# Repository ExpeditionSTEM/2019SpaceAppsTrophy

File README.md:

# 2019SpaceAppsTrophy

PLEASE STAY TUNED FOR UPDATES!  I WILL GET THIS REPO UPDATED BY 10/29.

A description of the 2019 Space Apps Trophy made for the Huntsville Main Stage

LIST OF COMPONENTS:

CUSTOM:

Custom Printed Circuit Board (PCB) - Designed by Andrew Denio.  Produced by JLCPCB.com  See "EAGLE" folder for files.

FROM ADAFRUIT:

Adafruit Feather 32u4 Bluefruit LE with Stacking Headers - Assembled (PID: 3242)
https://www.adafruit.com/product/3242

Adafruit 2.13" Monochrome eInk / ePaper Display FeatherWing - 250x122 Monochrome (PID: 4195)
https://www.adafruit.com/product/4195

Adafruit ADXL343 + ADT7410 Sensor FeatherWing (PID: 4147)
https://www.adafruit.com/product/4147

Adafruit 0.54" Quad Alphanumeric FeatherWing Display - Red (PID: 3130)
https://www.adafruit.com/product/3130

Lithium Ion Cylindrical Battery - 3.7v 2200mAh (PID: 1781)
https://www.adafruit.com/product/1781

FeatherWing Proto - Prototyping Add-on For All Feather Boards (PID: 2884)
https://www.adafruit.com/product/2884

Short Headers Kit for Feather - 12-pin + 16-pin Female Headers (PID: 2940)
https://www.adafruit.com/product/2940

Stacking Headers for Feather - 12-pin and 16-pin female headers (PID: 2830)
https://www.adafruit.com/product/2830

MISC:

Photoresistor (Light Sensor) 5 mm GM5539 5539
https://www.amazon.com/dp/B01N7V536K

Slide Switch 3 Pin 2 Position SPDT with PCB Panel for Arduino 0.5 Amp, 50V DC, 2 mm
https://www.amazon.com/gp/product/B079D58DB3/

FROM JLCPCB (mounted through SMT assembly):

WS2812B-V3 - 5050 LIGHT EMITTING DIODE (LED) RED/GREEN/BLUE SMD

TACTILE SWITCHES SPST 5.10MM X 5.10MM 0.40MM 50MA @ 12VDC SMD 

Multilayer Ceramic Capacitor - SMD/SMT 10UF 25V 0805 ROHS

CHIP RESISTOR - SURFACE MOUNT 10KOHMS ±1% 1/8W 0805 ROHS

CHIP RESISTOR - SURFACE MOUNT 470OHMS ±1% 1/8W 0805 ROHS

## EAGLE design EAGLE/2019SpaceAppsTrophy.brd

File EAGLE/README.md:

This folder contains the files needed to view the PCB in Autodesk Eagle

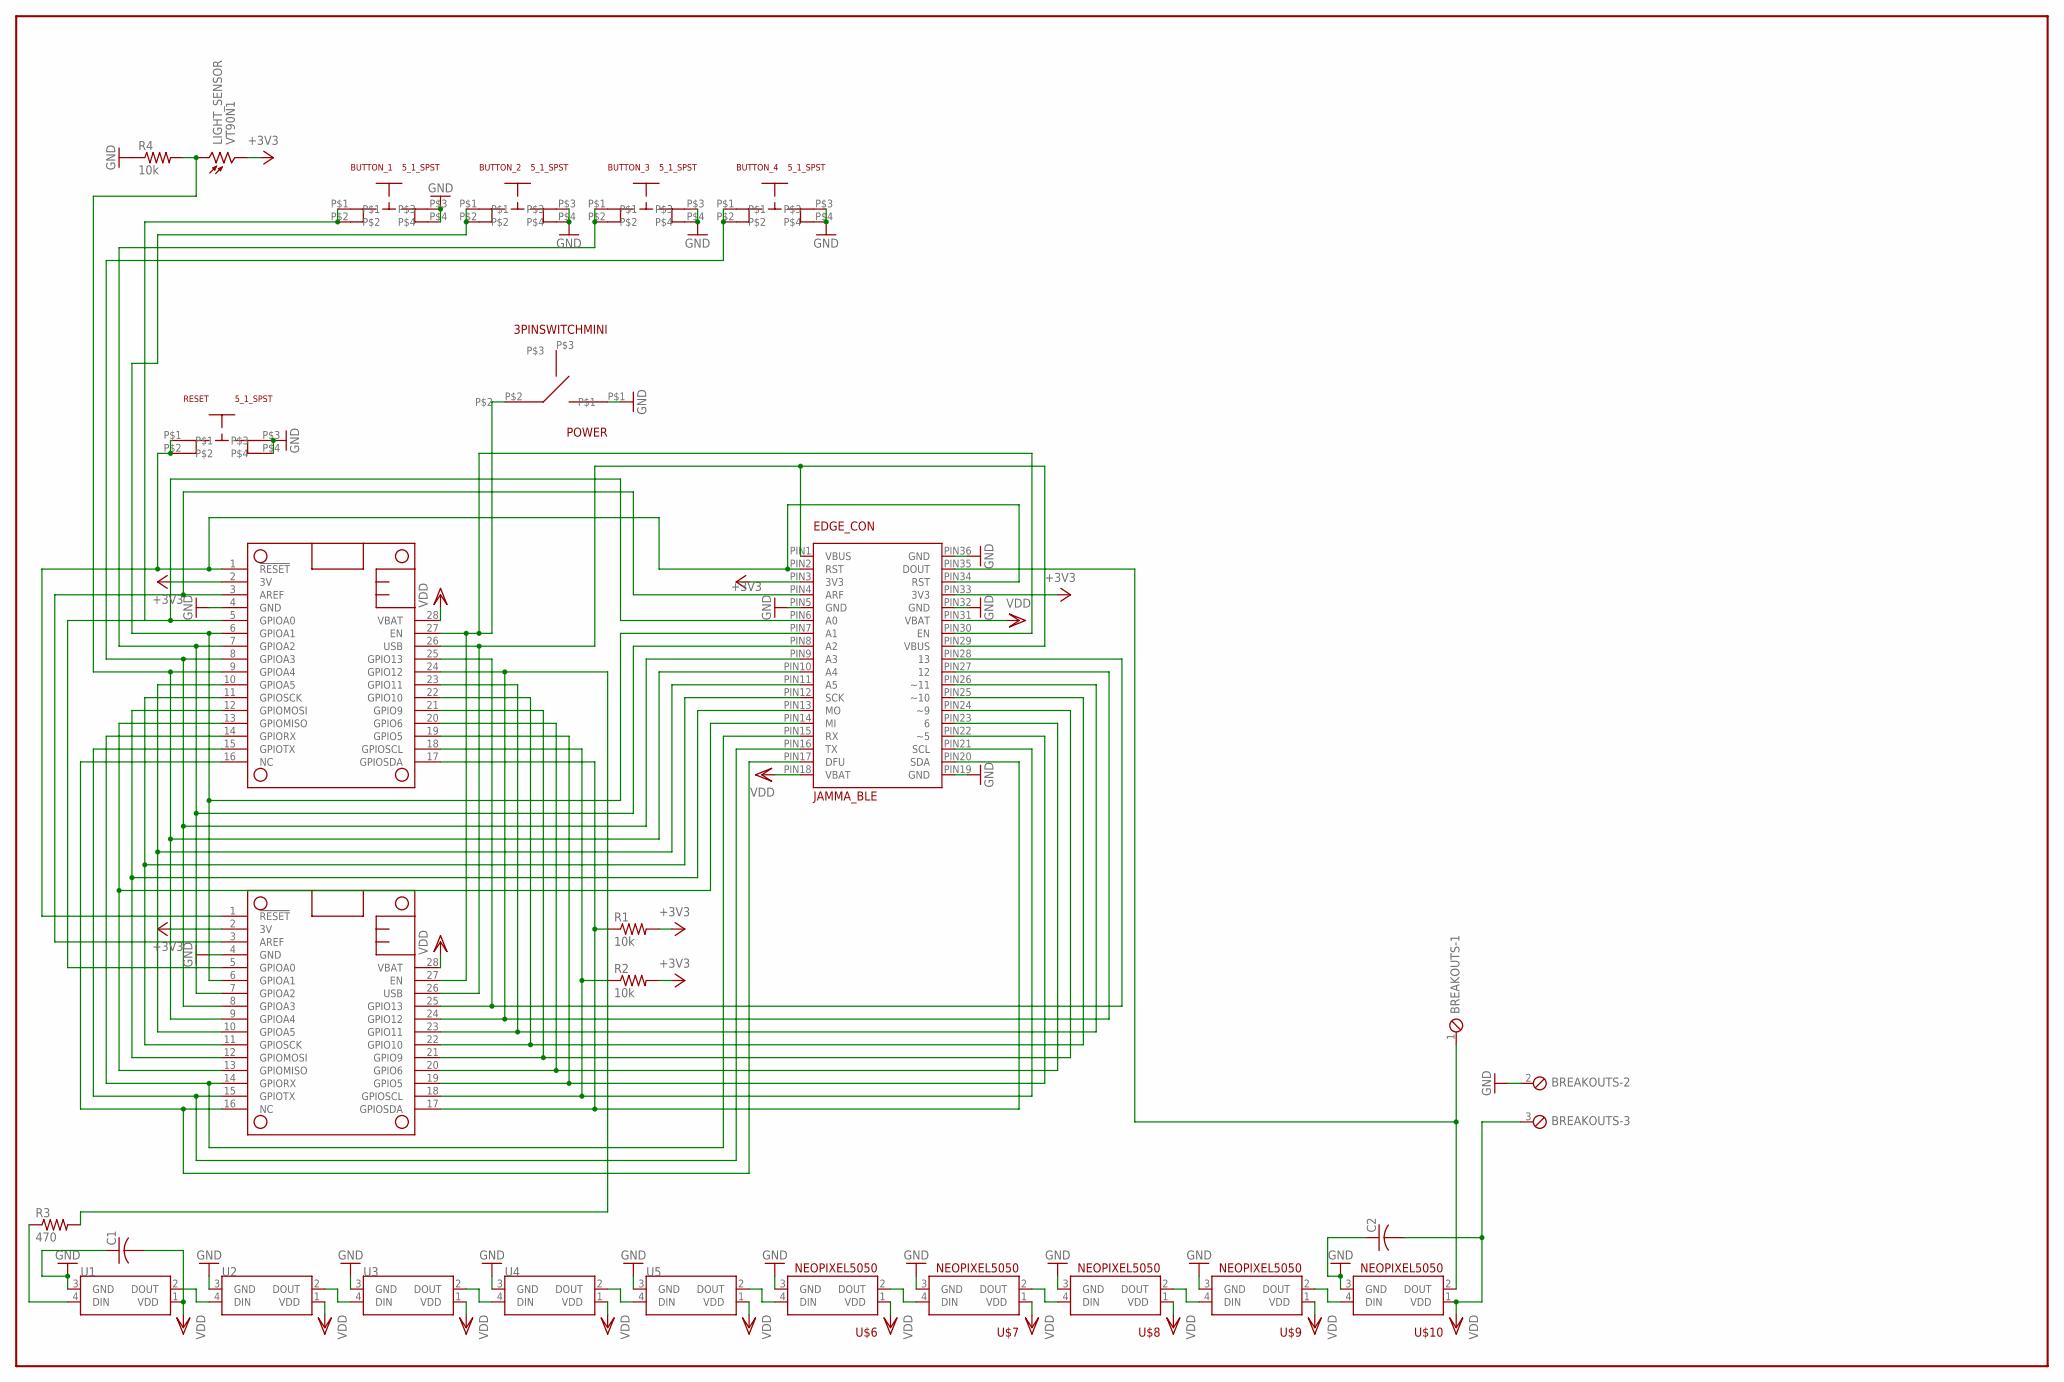
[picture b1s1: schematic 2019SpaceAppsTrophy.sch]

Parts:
BREAKOUTS: MPT3; 3POL254
BUTTON_1, BUTTON_2, BUTTON_3, BUTTON_4: 5_1_SPST
C1, C2: C-USC0805; C0805
EDGE_CON: JAMMA_BLE; JAMMA-28/56
LIGHT_SENSOR: VT90N1; VT900
MS2: FEATHERWING
POWER: 3PINSWITCHMINI; 3PINMINI
PROTOBOARD: FEATHERWING
R1, R2, R4: 10k; M0805
R3: 470; M0805
RESET: 5_1_SPST
U$1, U$2, U$3, U$4, U$5, U$6, U$7, U$8, U$9, U$10: NEOPIXEL5050

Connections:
+3V3: EDGE_CON.PIN3 (3V3), EDGE_CON.PIN33 (3V3), LIGHT_SENSOR.2, MS2.2 (3V), PROTOBOARD.2 (3V), R1.2, R2.2
GND: BREAKOUTS.2, BUTTON_1.P$3, BUTTON_1.P$4, BUTTON_2.P$3, BUTTON_2.P$4, BUTTON_3.P$3, BUTTON_3.P$4, BUTTON_4.P$3, BUTTON_4.P$4, C1.1, C2.1, EDGE_CON.PIN5 (GND), EDGE_CON.PIN19 (GND), EDGE_CON.PIN32 (GND), EDGE_CON.PIN36 (GND), MS2.4 (GND), POWER.P$1, PROTOBOARD.4 (GND), R4.1, RESET.P$3, RESET.P$4, U$1.3 (GND), U$2.3 (GND), U$3.3 (GND), U$4.3 (GND), U$5.3 (GND), U$6.3 (GND), U$7.3 (GND), U$8.3 (GND), U$9.3 (GND), U$10.3 (GND)
unnamed: EDGE_CON.PIN17 (DFU), MS2.16 (NC), PROTOBOARD.16 (NC)
unnamed: EDGE_CON.PIN16 (TX), MS2.15 (GPIOTX), PROTOBOARD.15 (GPIOTX)
unnamed: EDGE_CON.PIN15 (RX), MS2.14 (GPIORX), PROTOBOARD.14 (GPIORX)
unnamed: EDGE_CON.PIN14 (MI), MS2.13 (GPIOMISO), PROTOBOARD.13 (GPIOMISO)
unnamed: EDGE_CON.PIN13 (MO), MS2.12 (GPIOMOSI), PROTOBOARD.12 (GPIOMOSI)
unnamed: U$7.2 (DOUT), U$8.4 (DIN)
unnamed: EDGE_CON.PIN11 (A5), MS2.10 (GPIOA5), PROTOBOARD.10 (GPIOA5)
unnamed: EDGE_CON.PIN10 (A4), LIGHT_SENSOR.1, MS2.9 (GPIOA4), PROTOBOARD.9 (GPIOA4), R4.2
unnamed: BUTTON_4.P$1, BUTTON_4.P$2, EDGE_CON.PIN9 (A3), MS2.8 (GPIOA3), PROTOBOARD.8 (GPIOA3)
unnamed: BUTTON_3.P$1, BUTTON_3.P$2, EDGE_CON.PIN8 (A2), MS2.7 (GPIOA2), PROTOBOARD.7 (GPIOA2)
unnamed: BUTTON_2.P$1, BUTTON_2.P$2, EDGE_CON.PIN7 (A1), MS2.6 (GPIOA1), PROTOBOARD.6 (GPIOA1)
unnamed: BUTTON_1.P$1, BUTTON_1.P$2, EDGE_CON.PIN6 (A0), MS2.5 (GPIOA0), PROTOBOARD.5 (GPIOA0)
unnamed: EDGE_CON.PIN4 (ARF), MS2.3 (AREF), PROTOBOARD.3 (AREF)
unnamed: EDGE_CON.PIN2 (RST), EDGE_CON.PIN34 (RST), MS2.1 (!RESET), PROTOBOARD.1 (!RESET), RESET.P$1, RESET.P$2
unnamed: U$8.2 (DOUT), U$9.4 (DIN)
unnamed: EDGE_CON.PIN28 (13), MS2.25 (GPIO13), PROTOBOARD.25 (GPIO13)
unnamed: EDGE_CON.PIN27 (12), MS2.24 (GPIO12), PROTOBOARD.24 (GPIO12), R3.2
unnamed: EDGE_CON.PIN26 (~11), MS2.23 (GPIO11), PROTOBOARD.23 (GPIO11)
unnamed: EDGE_CON.PIN25 (~10), MS2.22 (GPIO10), PROTOBOARD.22 (GPIO10)
unnamed: EDGE_CON.PIN24 (~9), MS2.21 (GPIO9), PROTOBOARD.21 (GPIO9)
unnamed: EDGE_CON.PIN23 (6), MS2.20 (GPIO6), PROTOBOARD.20 (GPIO6)
unnamed: EDGE_CON.PIN22 (~5), MS2.19 (GPIO5), PROTOBOARD.19 (GPIO5)
unnamed: EDGE_CON.PIN21 (SCL), MS2.18 (GPIOSCL), PROTOBOARD.18 (GPIOSCL), R2.1
unnamed: EDGE_CON.PIN20 (SDA), MS2.17 (GPIOSDA), PROTOBOARD.17 (GPIOSDA), R1.1
unnamed: U$9.2 (DOUT), U$10.4 (DIN)
unnamed: U$1.2 (DOUT), U$2.4 (DIN)
unnamed: U$2.2 (DOUT), U$3.4 (DIN)
unnamed: U$3.2 (DOUT), U$4.4 (DIN)
unnamed: U$4.2 (DOUT), U$5.4 (DIN)
unnamed: U$6.2 (DOUT), U$7.4 (DIN)
unnamed: U$5.2 (DOUT), U$6.4 (DIN)
unnamed: BREAKOUTS.1, EDGE_CON.PIN35 (DOUT), U$10.2 (DOUT)
unnamed: EDGE_CON.PIN12 (SCK), MS2.11 (GPIOSCK), PROTOBOARD.11 (GPIOSCK)
unnamed: R3.1, U$1.4 (DIN)
unnamed: EDGE_CON.PIN30 (EN), MS2.27 (EN), POWER.P$2, PROTOBOARD.27 (EN)
USB: EDGE_CON.PIN1 (VBUS), EDGE_CON.PIN29 (VBUS), MS2.26 (USB), PROTOBOARD.26 (USB)
VDD: BREAKOUTS.3, C1.2, C2.2, EDGE_CON.PIN18 (VBAT), EDGE_CON.PIN31 (VBAT), MS2.28 (VBAT), PROTOBOARD.28 (VBAT), U$1.1 (VDD), U$2.1 (VDD), U$3.1 (VDD), U$4.1 (VDD), U$5.1 (VDD), U$6.1 (VDD), U$7.1 (VDD), U$8.1 (VDD), U$9.1 (VDD), U$10.1 (VDD)

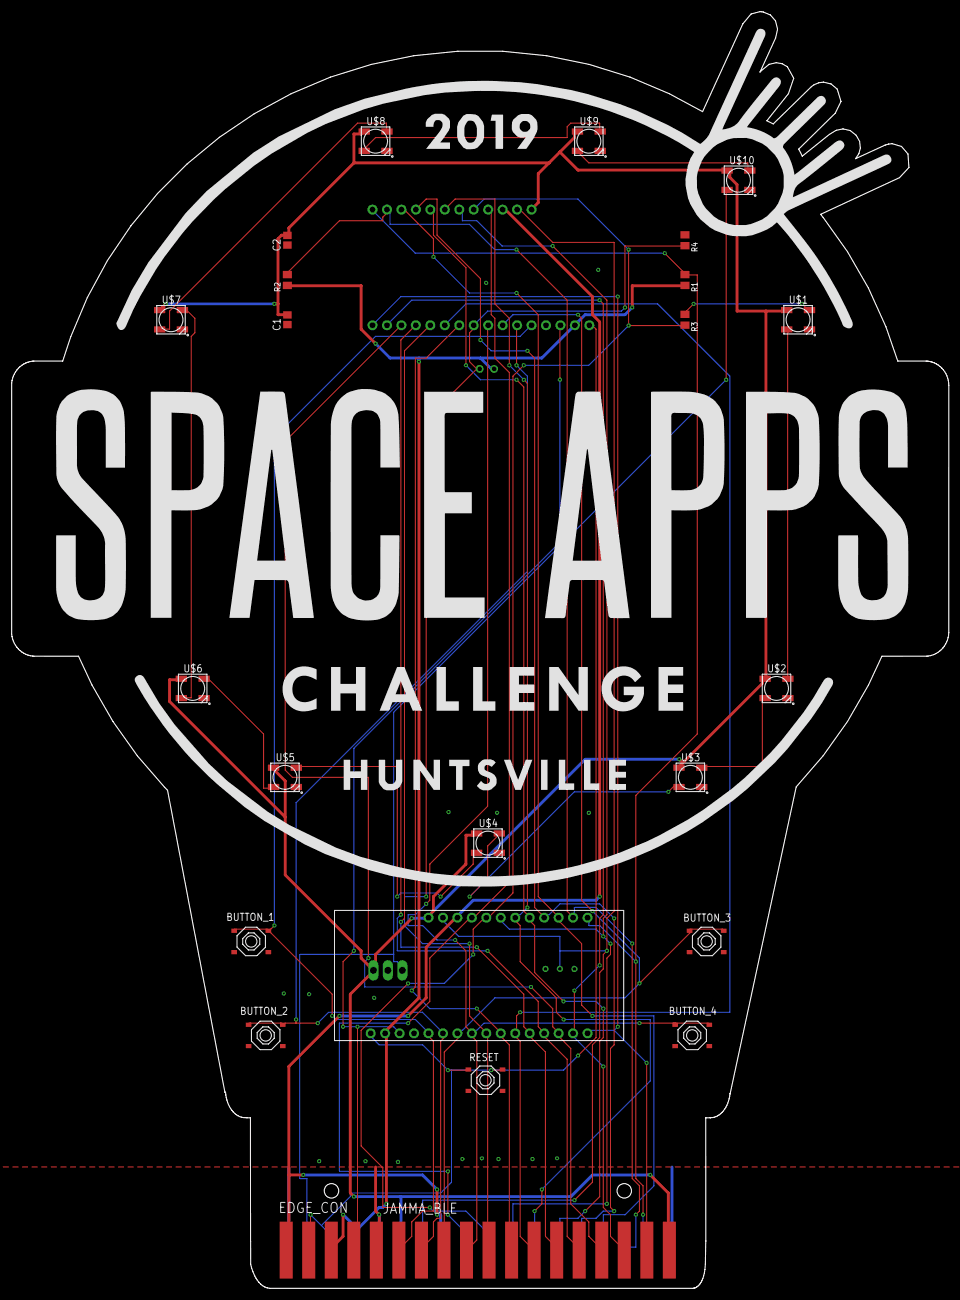
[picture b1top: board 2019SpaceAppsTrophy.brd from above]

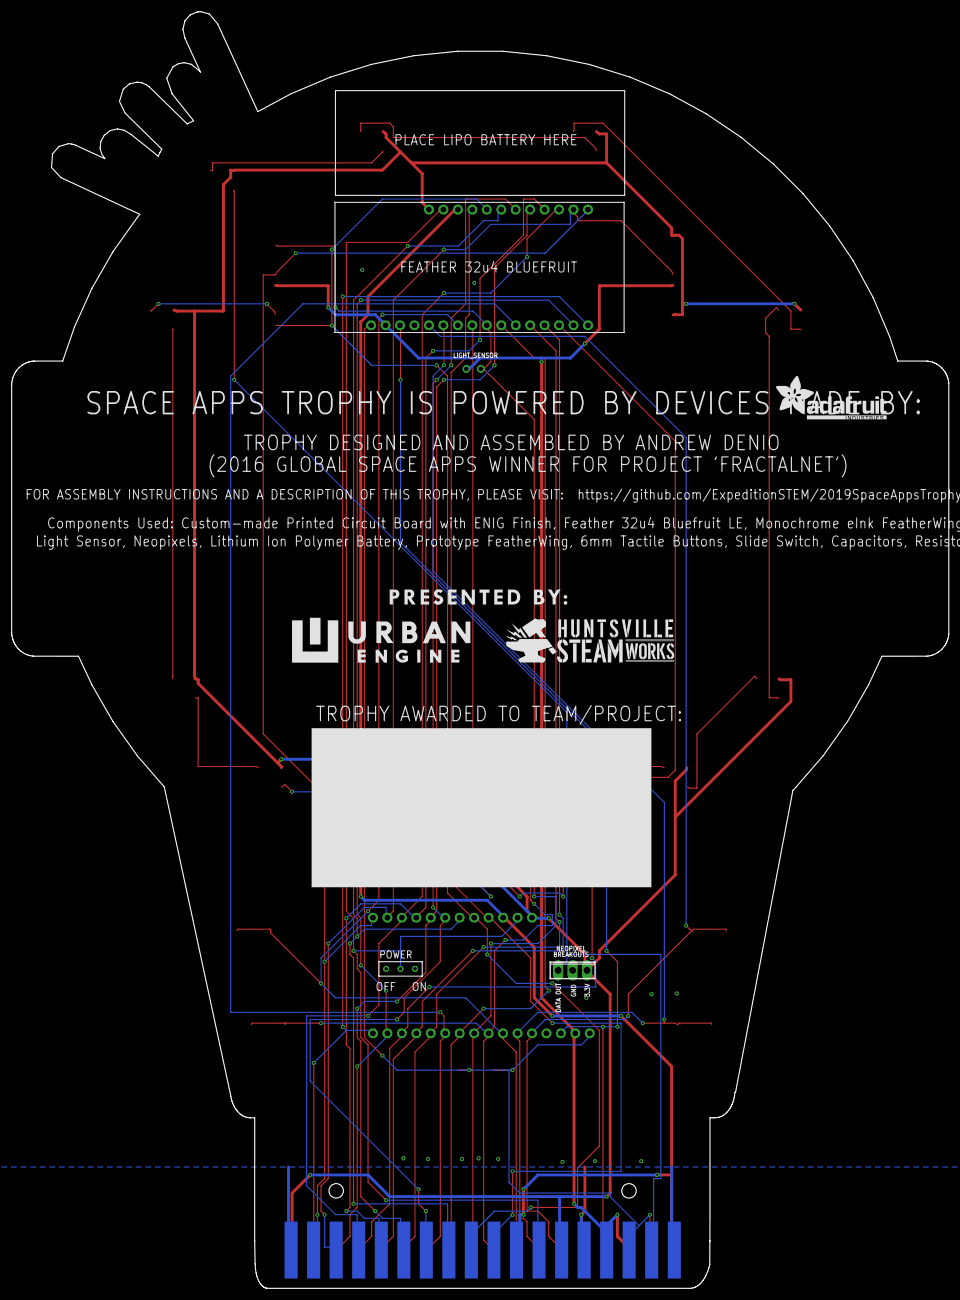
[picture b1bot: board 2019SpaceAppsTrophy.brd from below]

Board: 2 copper layers, 164.6 x 224.3 mm, 28 parts (5 on the bottom side), 39 nets.

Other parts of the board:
U$28: ADAFRUIT_TEXT_20MM

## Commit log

2019-10-08 Add files via upload
    Build of Materials for Trophy - Excel format for JLCPCB
2019-10-08 Add files via upload
    SMD/SMT Mounting File for Trophy - Used for JLCPCB
2019-10-08 Create test

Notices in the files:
parts and their libraries:
microbuilder: This work is placed in the public domain, and may be freely used for commercial and non-commercial work with the following conditions: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
